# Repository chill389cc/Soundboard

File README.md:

# Soundboard
Code and schematics for a macropad soundboard system for the office bullpen

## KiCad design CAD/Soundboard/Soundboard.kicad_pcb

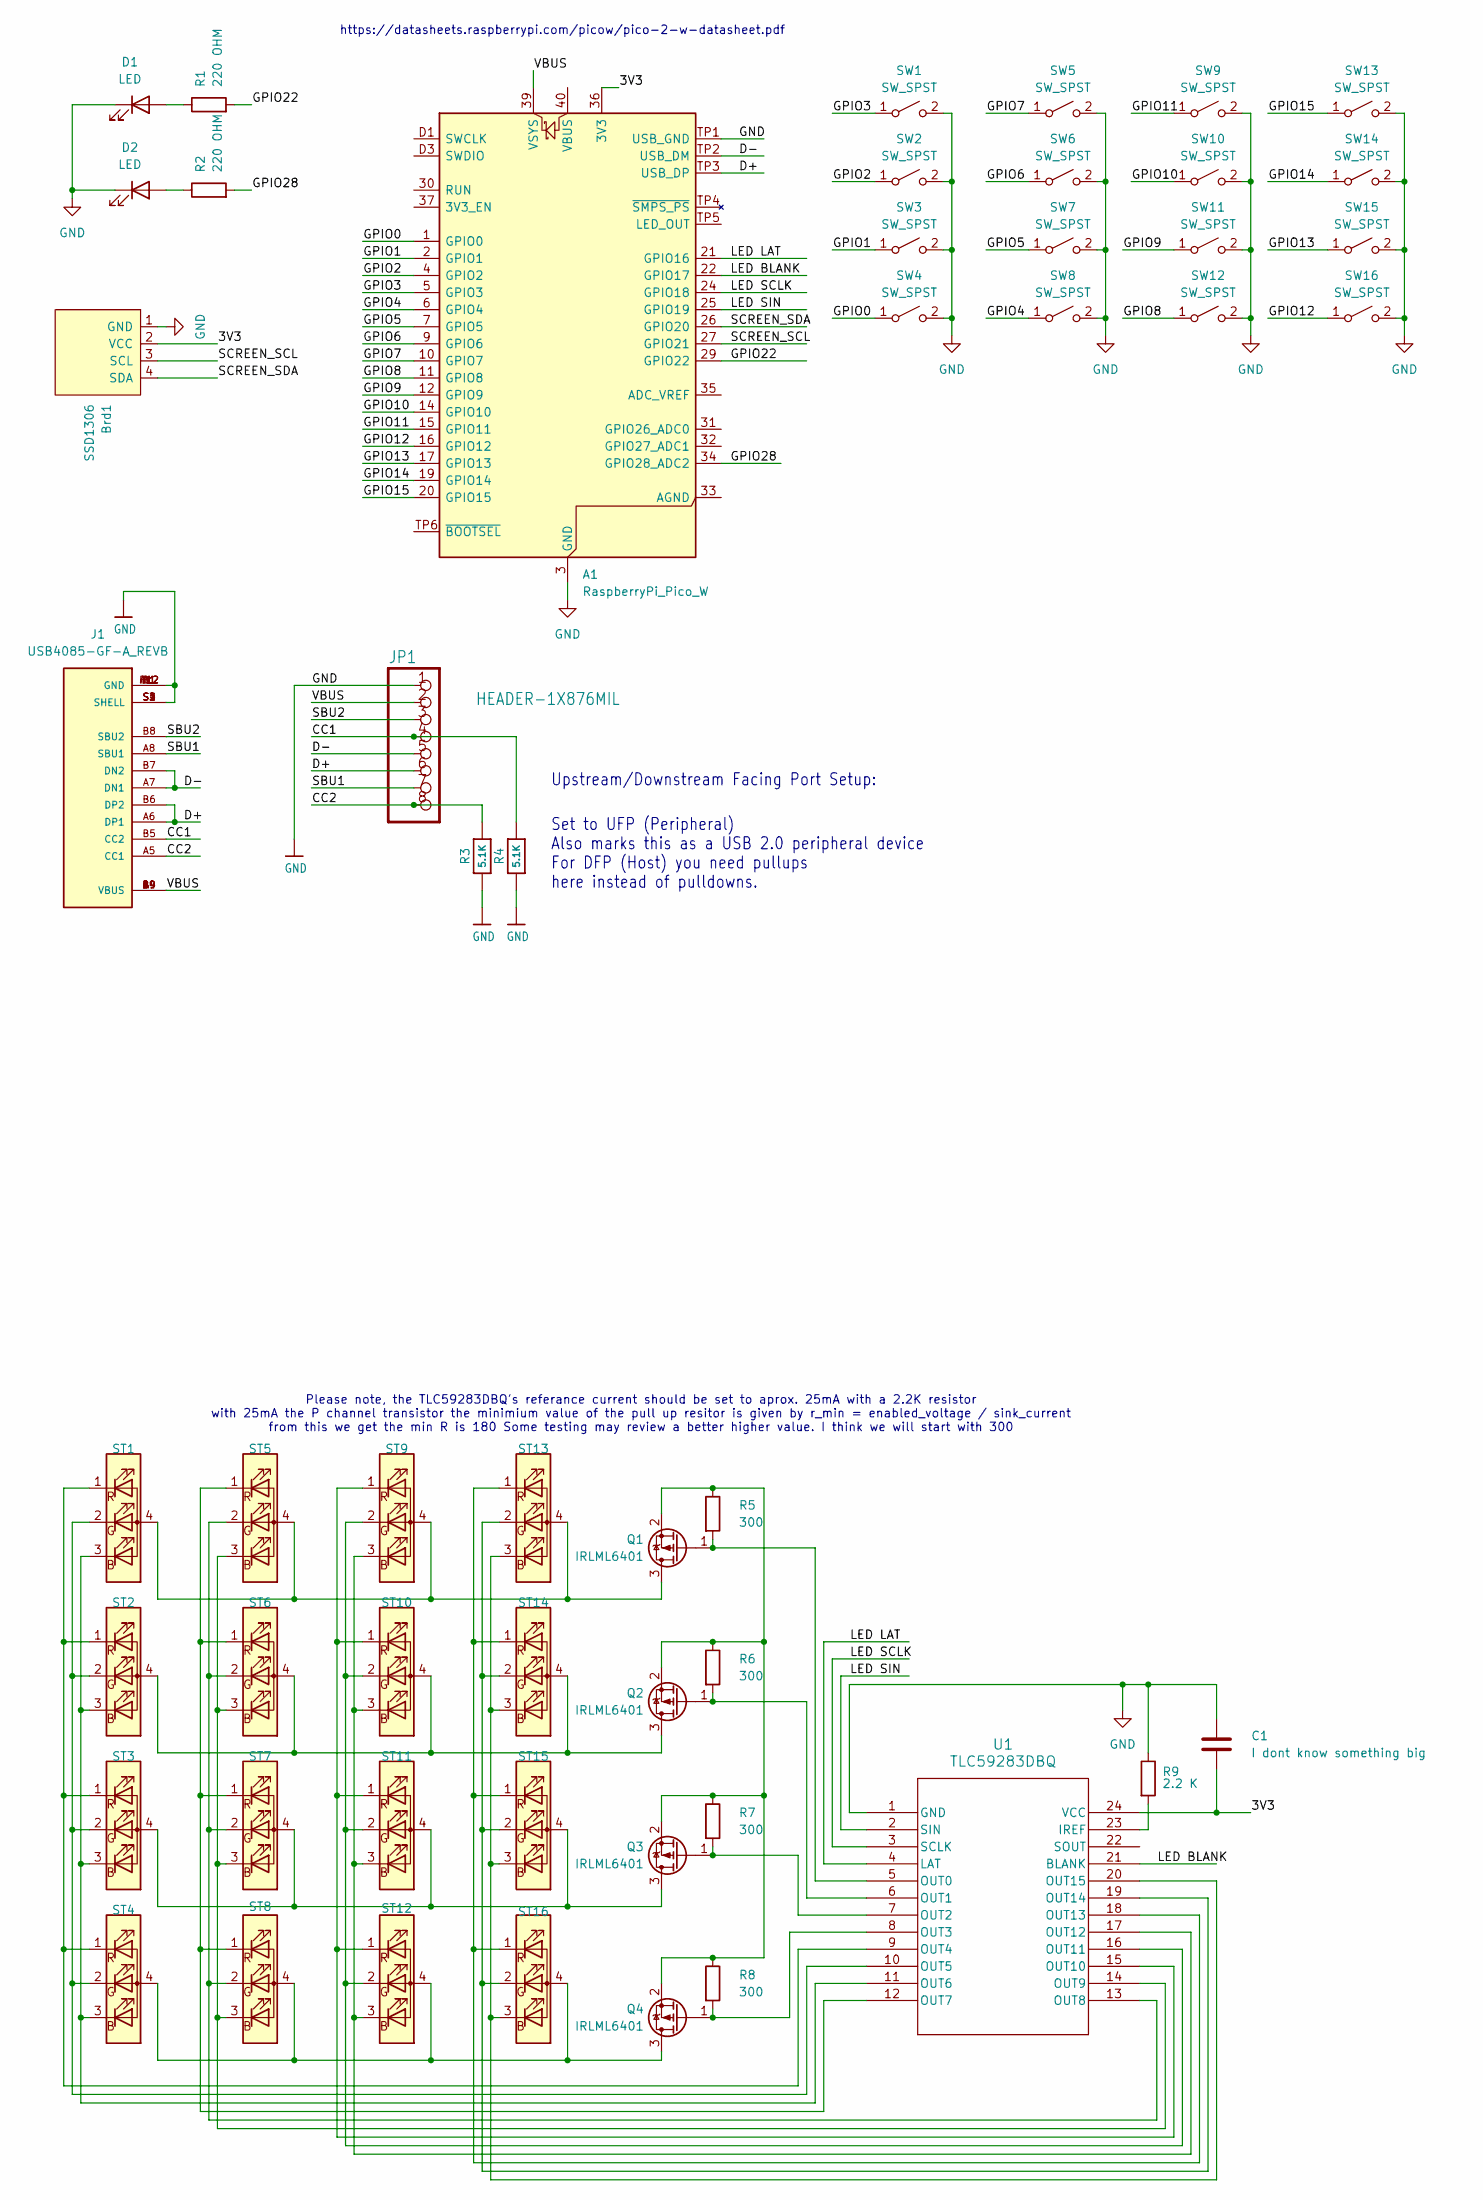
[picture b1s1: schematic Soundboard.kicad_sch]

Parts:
A1: RaspberryPi_Pico_W; RaspberryPi_Pico_W_SMD
Brd1: SSD1306; Adafruit_SSD1306
C1: I dont know something big; C_0805_2012Metric
D1, D2: LED; LED_D5.0mm_Clear
J1: USB4085-GF-A_REVB; GCT_USB4085-GF-A_REVB; PARTREV B
JP1: HEADER-1X876MIL; PinHeader_1x08_P2.54mm_Vertical
Q1, Q2, Q3, Q4: IRLML6401; SOT-23
R1, R2: 220 OHM; R_Axial_DIN0204_L3.6mm_D1.6mm_P7.62mm_Horizontal
R3, R4: 5.1K; R_0805_2012Metric
R5, R6, R7, R8: 300; R_0805_2012Metric
R9: 2.2 K; R_0805_2012Metric
ST1, ST2, ST3, ST4, ST5, ST6, ST7, ST8, ST9, ST10, ST11, ST12, ST13, ST14, ST15, ST16: ASMB-MTB1-0A3A2; LED_Avago_PLCC4_3.2x2.8mm_CW
SW1, SW2, SW3, SW4, SW5, SW6, SW7, SW8, SW9, SW10, SW11, SW12, SW13, SW14, SW15, SW16: SW_SPST; SW_Cherry_MX_PCB_1.00u
U1: TLC59283DBQ; DBQ24_TEX

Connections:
/3V3: A1.36 (3V3), Brd1.2 (VCC), C1.2, U1.24 (VCC)
/CC1: J1.B5 (CC2), JP1.4, R4.2
/CC2: J1.A5 (CC1), JP1.8, R3.2
/D+: A1.TP3 (USB_DP), J1.A6 (DP1), J1.B6 (DP2), JP1.6
/D-: A1.TP2 (USB_DM), J1.A7 (DN1), J1.B7 (DN2), JP1.5
/GPIO0: A1.1 (GPIO0), SW4.1 (A)
/GPIO1: A1.2 (GPIO1), SW3.1 (A)
/GPIO2: A1.4 (GPIO2), SW2.1 (A)
/GPIO3: A1.5 (GPIO3), SW1.1 (A)
/GPIO4: A1.6 (GPIO4), SW8.1 (A)
/GPIO5: A1.7 (GPIO5), SW7.1 (A)
/GPIO6: A1.9 (GPIO6), SW6.1 (A)
/GPIO7: A1.10 (GPIO7), SW5.1 (A)
/GPIO8: A1.11 (GPIO8), SW12.1 (A)
/GPIO9: A1.12 (GPIO9), SW11.1 (A)
/GPIO10: A1.14 (GPIO10), SW10.1 (A)
/GPIO11: A1.15 (GPIO11), SW9.1 (A)
/GPIO12: A1.16 (GPIO12), SW16.1 (A)
/GPIO13: A1.17 (GPIO13), SW15.1 (A)
/GPIO14: A1.19 (GPIO14), SW14.1 (A)
/GPIO15: A1.20 (GPIO15), SW13.1 (A)
/GPIO22: A1.29 (GPIO22), R1.2
/GPIO28: A1.34 (GPIO28_ADC2), R2.2
/LED BLANK: A1.22 (GPIO17), U1.21 (BLANK)
/LED LAT: A1.21 (GPIO16), U1.4 (LAT)
/LED SCLK: A1.24 (GPIO18), U1.3 (SCLK)
/LED SIN: A1.25 (GPIO19), U1.2 (SIN)
/SBU1: J1.A8 (SBU1), JP1.7
/SBU2: J1.B8 (SBU2), JP1.3
/SCREEN_SCL: A1.27 (GPIO21), Brd1.3 (SCL)
/SCREEN_SDA: A1.26 (GPIO20), Brd1.4 (SDA)
/VBUS: A1.39 (VSYS), J1.A4 (VBUS), J1.A9 (VBUS), J1.B4 (VBUS), J1.B9 (VBUS), JP1.2
GND: A1.3 (GND), A1.8 (GND), A1.13 (GND), A1.18 (GND), A1.23 (GND), A1.28 (GND), A1.38 (GND), A1.D2 (GND), A1.TP1 (USB_GND), Brd1.1 (GND), C1.1, D1.1 (K), D2.1 (K), J1.A1 (GND), J1.A12 (GND), J1.B1 (GND), J1.B12 (GND), J1.S1 (SHELL), J1.S2 (SHELL), J1.S3 (SHELL), J1.S4 (SHELL), JP1.1, R3.1, R4.1, R9.1, SW1.2 (B), SW2.2 (B), SW3.2 (B), SW4.2 (B), SW5.2 (B), SW6.2 (B), SW7.2 (B), SW8.2 (B), SW9.2 (B), SW10.2 (B), SW11.2 (B), SW12.2 (B), SW13.2 (B), SW14.2 (B), SW15.2 (B), SW16.2 (B), U1.1 (GND)
unnamed: D1.2 (A), R1.1
unnamed: D2.2 (A), R2.1
unnamed: Q1.3 (D), ST1.4 (A), ST5.4 (A), ST9.4 (A), ST13.4 (A)
unnamed: Q1.1 (G), R5.2, U1.5 (OUT0)
unnamed: Q1.2 (S), Q2.2 (S), Q3.2 (S), Q4.2 (S), R5.1, R6.1, R7.1, R8.1
unnamed: Q2.3 (D), ST2.4 (A), ST6.4 (A), ST10.4 (A), ST14.4 (A)
unnamed: Q2.1 (G), R6.2, U1.6 (OUT1)
unnamed: Q3.3 (D), ST3.4 (A), ST7.4 (A), ST11.4 (A), ST15.4 (A)
unnamed: Q3.1 (G), R7.2, U1.7 (OUT2)
unnamed: Q4.3 (D), ST4.4 (A), ST8.4 (A), ST12.4 (A), ST16.4 (A)
unnamed: Q4.1 (G), R8.2, U1.8 (OUT3)
unnamed: ST1.3 (BK), ST2.3 (BK), ST3.3 (BK), ST4.3 (BK), U1.11 (OUT6)
unnamed: ST1.2 (GK), ST2.2 (GK), ST3.2 (GK), ST4.2 (GK), U1.10 (OUT5)
unnamed: ST1.1 (RK), ST2.1 (RK), ST3.1 (RK), ST4.1 (RK), U1.9 (OUT4)
unnamed: ST5.3 (BK), ST6.3 (BK), ST7.3 (BK), ST8.3 (BK), U1.14 (OUT9)
unnamed: ST5.2 (GK), ST6.2 (GK), ST7.2 (GK), ST8.2 (GK), U1.13 (OUT8)
unnamed: ST5.1 (RK), ST6.1 (RK), ST7.1 (RK), ST8.1 (RK), U1.12 (OUT7)
unnamed: ST9.3 (BK), ST10.3 (BK), ST11.3 (BK), ST12.3 (BK), U1.17 (OUT12)
unnamed: ST9.2 (GK), ST10.2 (GK), ST11.2 (GK), ST12.2 (GK), U1.16 (OUT11)
unnamed: ST9.1 (RK), ST10.1 (RK), ST11.1 (RK), ST12.1 (RK), U1.15 (OUT10)
unnamed: ST13.3 (BK), ST14.3 (BK), ST15.3 (BK), ST16.3 (BK), U1.20 (OUT15)
unnamed: ST13.2 (GK), ST14.2 (GK), ST15.2 (GK), ST16.2 (GK), U1.19 (OUT14)
unnamed: ST13.1 (RK), ST14.1 (RK), ST15.1 (RK), ST16.1 (RK), U1.18 (OUT13)
unnamed: R9.2, U1.23 (IREF)

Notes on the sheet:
https://datasheets.raspberrypi.com/picow/pico-2-w-datasheet.pdf
Upstream/Downstream Facing Port Setup:
Please note, the TLC59283DBQ's referance current should be set to aprox. 25mA with a 2.2K resistor with 25mA the P channel transistor the minimium value of the pull up resitor is given by r_min = enabled_voltage / sink_current from this we get the min R is 180 Some testing may review a better highe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
Set to UFP (Peripheral) Also marks this as a USB 2.0 peripheral device For DFP (Host) you need pullups here instead of pulldowns.

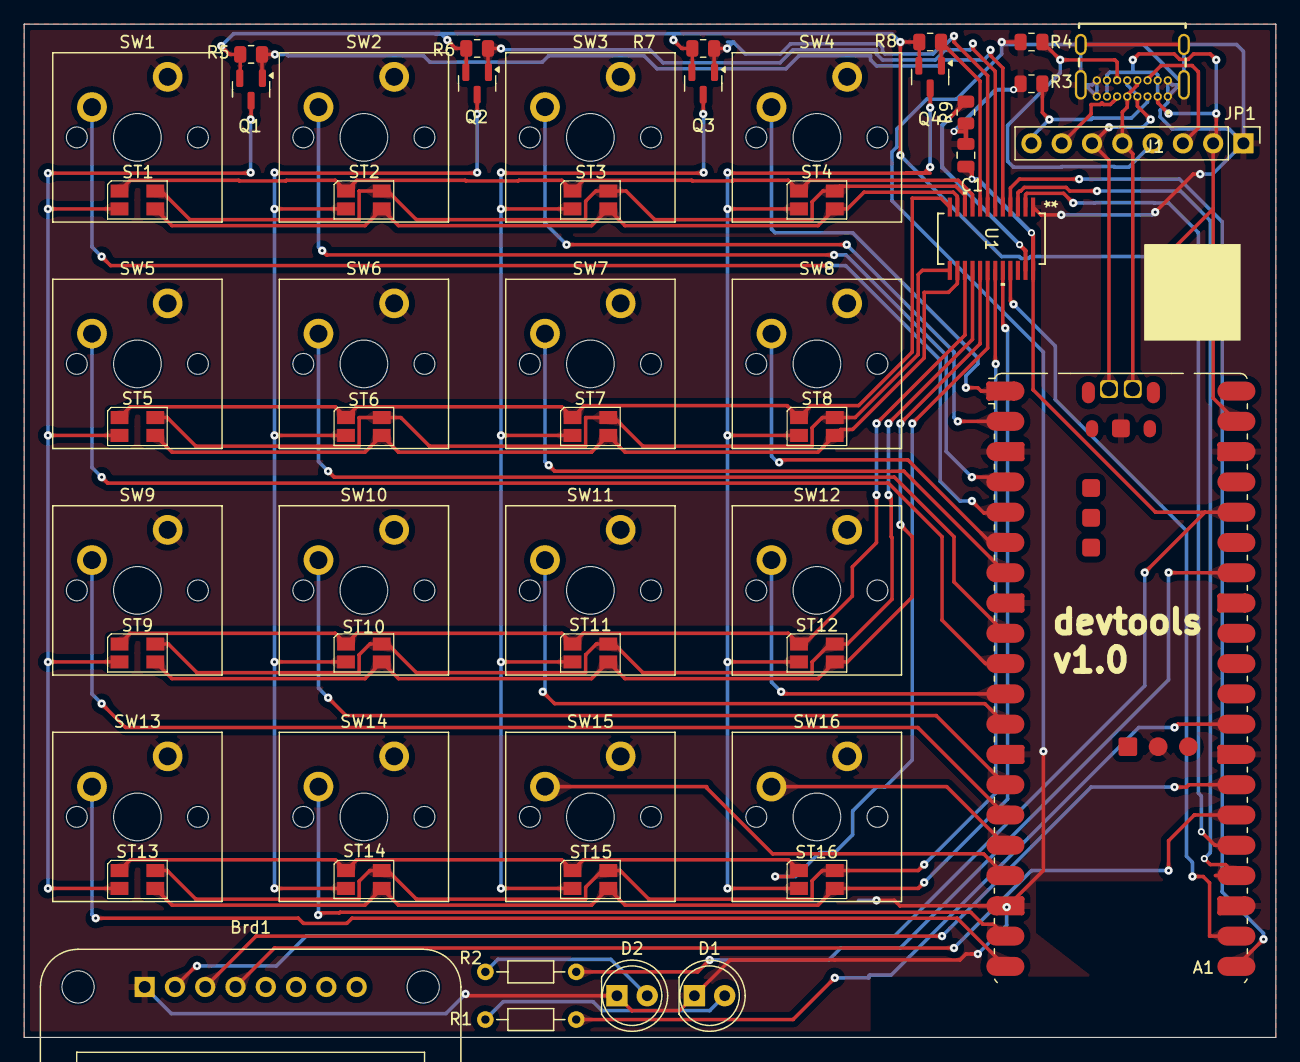
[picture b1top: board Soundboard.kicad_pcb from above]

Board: 2 copper layers, 105.0 x 85.0 mm, 53 parts (0 on the bottom side), 57 nets.

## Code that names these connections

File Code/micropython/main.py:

# from typing import Callable, Optional
import time
import random
from machine import SPI, Pin
import asyncio


def lin_to_pos(lin) -> tuple[int,int]:
   y = int(lin % 4)
   x = int((lin - y) / 4)
   return (x,y)

def pos_to_lin(x,y) -> int:
   lin = x*4 + y
   return lin

class LedMatrix:
  # These are the write line for the led matrix, the first 12 values are RGB values
  # The last 4 bits signal what column is active. Technically any number of columns can be active
  # but for simplicity we activate one at a time. :shrug:    
  _lines = [[0,0,0,0,0,0,0,0,0,0,0,0],
            [0,0,0,0,0,0,0,0,0,0,0,0],
            [0,0,0,0,0,0,0,0,0,0,0,0],
            [0,0,0,0,0,0,0,0,0,0,0,0]]
  _line_markers = [[1,0,0,0],
                   [0,1,0,0],
                   [0,0,1,0],
                   [0,0,0,1]]
  # frame scale sets the color scale. ex. a scale of 10 would allow each color to range from 0-10
  _frame_scale = 10

  _PIN_LATCH:Pin
  _PIN_BLANK:Pin
  _PIN_DATA:Pin
  _PIN_CLOCK:Pin

  def __init__(self, latch_pin:Pin, blank_pin:Pin, data_pin:Pin, clock_pin:Pin):
     self._PIN_LATCH = latch_pin
     self._PIN_BLANK = blank_pin
     self._PIN_DATA = data_pin
     self._PIN_CLOCK = clock_pin
     latch_pin.value(0)

  def _write_shift_register(self, line:list[int], line_marker:list[int],cutoff:int):
    for val in line:
      self._PIN_CLOCK.value(0)
      self._PIN_DATA.value(bool(val >= cutoff))
      self._PIN_CLOCK.value(1)
    for val in line_marker:
      self._PIN_CLOCK.value(0)
      self._PIN_DATA.value(val)
      self._PIN_CLOCK.value(1)
    
    self._PIN_LATCH.value(1)
    self._PIN_LATCH.value(0)

  def set_pixel(self,x,y,r,g,b):
    self._lines[x][3*y + 0] = r
    self._lines[x][3*y + 1] = g
    self._lines[x][3*y + 2] = b

  def set_pixel_lin(self,i,r,b,g):
    x,y = lin_to_pos(i)
    self.set_pixel(x,y,r,b,g)

  async def display_loop(self):
    while True:
      for cutoff in range(self._frame_scale):
        for i in range(4):
            self._write_shift_register(self._lines[i],self._line_markers[i],cutoff+1)
            # print(f"writing line:{line} with cutoff:{cutoff}")
            # Let another thread take a moment

      await asyncio.sleep(0)
      # print("display")

class AsyncKeys:
  _buttons:list[Pin]
  _button_state:list[bool]

  @staticmethod
  def _make_handler(i:int, custom_handler):
    def handler(t:Pin):
      if custom_handler:
        custom_handler(i,t)
    return handler

  def __init__(self, pin_numbers: list[int],optional_handler=None) -> None:
      self._buttons = []
      self._button_map = {}
      self._button_state = []
      for i in pin_numbers:
        pinName = f"GPIO{i}"
        pin = Pin(pinName,Pin.IN,Pin.PULL_UP)
        print(f"initializing \"{pinName}\"")
        index = len(self._buttons)
        pin.irq(self._make_handler(index,optional_handler))
        self._buttons.append(pin)

# LED_LAT = Pin("GPIO16",Pin.OUT)
# LED_BLANK = Pin("GPIO17",Pin.OUT)
# LED_BLANK.value(0)
# LED_SIN = Pin("GPIO18",Pin.OUT)
# LED_SCLK = Pin("GPIO19",Pin.OUT)

leds = LedMatrix(Pin("GPIO16",Pin.OUT) , Pin("GPIO17",Pin.OUT),Pin("GPIO18",Pin.OUT),Pin("GPIO19",Pin.OUT))

def key_handler(index:int,pin:Pin):
  button_on = not pin.value()
  r = int(random.random()*leds._frame_scale) if button_on else 0
  g = int(random.random()*leds._frame_scale) if button_on else 0
  b = int(random.random()*leds._frame_scale) if button_on else 0
  leds.set_pixel_lin(index,r,g,b)
  # print(f"set led:{index} to {{{r},{g},{b}}}")


keys = AsyncKeys([12,8,4,0,13,9,5,1,14,10,6,2,15,11,7,3], key_handler)

# SW = [
#   Pin("GPIO12",Pin.IN,Pin.PULL_UP),
#   Pin("GPIO8",Pin.IN,Pin.PULL_UP),
#   Pin("GPIO4",Pin.IN,Pin.PULL_UP),
#   Pin("GPIO0",Pin.IN,Pin.PULL_UP),
#   Pin("GPIO13",Pin.IN,Pin.PULL_UP),
#   Pin("GPIO9",Pin.IN,Pin.PULL_UP),
#   Pin("GPIO5",Pin.IN,Pin.PULL_UP),
#   Pin("GPIO1",Pin.IN,Pin.PULL_UP),
#   Pin("GPIO14",Pin.IN,Pin.PULL_UP),
#   Pin("GPIO10",Pin.IN,Pin.PULL_UP),
#   Pin("GPIO6",Pin.IN,Pin.PULL_UP),
#   Pin("GPIO2",Pin.IN,Pin.PULL_UP),
#   Pin("GPIO15",Pin.IN,Pin.PULL_UP),
#   Pin("GPIO11",Pin.IN,Pin.PULL_UP),
#   Pin("GPIO7",Pin.IN,Pin.PULL_UP),
#   Pin("GPIO3",Pin.IN,Pin.PULL_UP)
# ] 



# for i in range(16):
#   SW[i].irq(make_handler(i))

# def _set_leds(array_vals,scale = 1):
#   for val in array_vals:
#     LED_SCLK.value(0)
#     LED_SIN.value(val >= scale)
#     LED_SCLK.value(1)
#   LED_LAT.value(1)
#   LED_LAT.value(0)

async def main():
    asyncio.create_task(leds.display_loop())
    while True:
      # for col in [0,1,2,3]:
      #   print(f"testing {col}")
      #   set_pixel(col,0,1,0,0)
      #   set_pixel(col,1,0,1,0)
      #   set_pixel(col,2,1,1,0)
      #   set_pixel(col,3,0,0,1)
      #   set_pixel(col-1 if col > 0 else 3,0,0,0,0)
      #   set_pixel(col-1 if col > 0 else 3,1,0,0,0)
      #   set_pixel(col-1 if col > 0 else 3,2,0,0,0)
      #   set_pixel(col-1 if col > 0 else 3,3,0,0,0)
      #   await asyncio.sleep_ms(500)
        # for lin in range(16):
        #   set_pixel_lin((lin+0)%16,0,0,0)
        #   set_pixel_lin((lin+1)%16,1,0,0)
        #   set_pixel_lin((lin+2)%16,0,1,0)
        #   set_pixel_lin((lin+3)%16,1,1,0)
        #   set_pixel_lin((lin+4)%16,0,0,1)
        #   set_pixel_lin((lin+5)%16,1,0,1)
        #   set_pixel_lin((lin+6)%16,0,1,1)
        #   set_pixel_lin((lin+7)%16,1,1,1)
        #   await asyncio.sleep_ms(50)


    #   if not _buttons[0]:
    #     for lin in range(15):
    #       set_pixel_lin(lin,0,0,0)
    #       set_pixel_lin((lin+1)%16,1,0,0)
    #       set_pixel_lin((lin+2)%16,0,1,0)
    #       set_pixel_lin((lin+3)%16,1,1,0)
    #       set_pixel_lin((lin+4)%16,0,0,1)
    #       set_pixel_lin((lin+5)%16,1,0,1)
    #       set_pixel_lin((lin+6)%16,0,1,1)
    #       set_pixel_lin((lin+7)%16,1,1,1)
    #       await asyncio.sleep_ms(50)
    #   else:
          await asyncio.sleep_ms(50)


# def test_red_leds():
#   _set_leds([1,0,0,1,0,0,1,0,0,1,0,0,1,0,0,0])
#   time.sleep_ms(500)
#   _set_leds([1,0,0,1,0,0,1,0,0,1,0,0,0,1,0,0])
#   time.sleep_ms(500)
#   _set_leds([1,0,0,1,0,0,1,0,0,1,0,0,0,0,1,0])
#   time.sleep_ms(500)
#   _set_leds([1,0,0,1,0,0,1,0,0,1,0,0,0,0,0,1])
#   time.sleep_ms(500)

# def test_green_leds():
#   _set_leds([0,1,0,0,1,0,0,1,0,0,1,0,1,0,0,0])
#   time.sleep_ms(500)
#   _set_leds([0,1,0,0,1,0,0,1,0,0,1,0,0,1,0,0])
#   time.sleep_ms(500)
#   _set_leds([0,1,0,0,1,0,0,1,0,0,1,0,0,0,1,0])
#   time.sleep_ms(500)
#   _set_leds([0,1,0,0,1,0,0,1,0,0,1,0,0,0,0,1])
#   time.sleep_ms(500)

# def test_blue_leds():
#   _set_leds([0,0,1,0,0,1,0,0,1,0,0,1,1,0,0,0])
#   time.sleep_ms(500)
#   _set_leds([0,0,1,0,0,1,0,0,1,0,0,1,0,1,0,0])
#   time.sleep_ms(500)
#   _set_leds([0,0,1,0,0,1,0,0,1,0,0,1,0,0,1,0])
#   time.sleep_ms(500)
#   _set_leds([0,0,1,0,0,1,0,0,1,0,0,1,0,0,0,1])
#   time.sleep_ms(500)

asyncio.run(main())

# while True:
#   test_red_leds()
#   test_green_leds()
#   test_blue_leds()

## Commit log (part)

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2025-04-26 initial schematic
2025-04-26 add sample python scripts
2025-04-27 fix maybeneeded zip
2025-04-28 add the libs as submodules
2025-04-28 move it to a better place
2025-04-28 remove empty zip
2025-04-28 add missing libarary
2025-04-28 use libraries
2025-04-28 add a default layout without routing
2025-04-30 add some libs
2025-04-30 big changes boys
2025-05-01 do all the things
2025-05-20 add a bunch of submodule repos, add some fancy plexing circuits place and route
2025-05-29 add demo file
2025-05-31 just some cody mc code face
2025-09-11 swap led sclk and sin
2025-10-21 move some caps
2025-11-08 code
